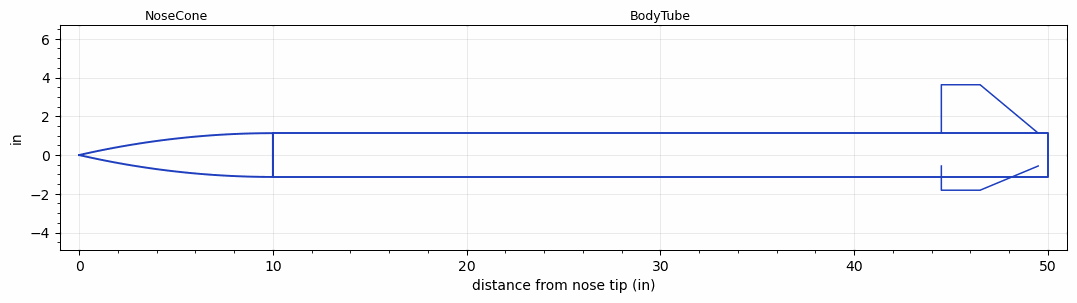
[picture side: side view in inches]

<RASAeroDocument>
 <FileVersion>2</FileVersion>
 <RocketDesign>
  <NoseCone>
   <Length>10</Length>
   <Diameter>2.26</Diameter>
   <Shape>Tangent Ogive</Shape>
   <Location>0</Location>
  </NoseCone>
  <BodyTube>
   <Length>39.9999</Length>
   <Diameter>2.26</Diameter>
   <Location>10</Location>
   <Fin>
    <Count>3</Count>
    <Chord>5</Chord>
    <Span>2.5</Span>
    <SweepDistance>0</SweepDistance>
    <TipChord>2</TipChord>
    <Thickness>0.125</Thickness>
    <Location>5.5</Location>
    <AirfoilSection>Square</AirfoilSection>
   </Fin>
  </BodyTube>
  <Surface>Smooth (Zero Roughness)</Surface>
  <ModifiedBarrowman>False</ModifiedBarrowman>
  <Turbulence>True</Turbulence>
  <UseBooster1>False</UseBooster1>
  <UseBooster2>False</UseBooster2>
  <Comments>Controlled aerodynamic investigation: Ssq-unswept</Comments>
 </RocketDesign>
 <LaunchSite>
  <Altitude>0</Altitude>
  <Pressure>29.9214</Pressure>
  <RodAngle>0</RodAngle>
  <RodLength>6.5617</RodLength>
  <Temperature>59</Temperature>
  <WindSpeed>0</WindSpeed>
 </LaunchSite>
 <Recovery>
  <Altitude1>656.168</Altitude1>
  <Altitude2>0</Altitude2>
  <DeviceType1>Parachute</DeviceType1>
  <DeviceType2>None</DeviceType2>
  <Event1>True</Event1>
  <Event2>False</Event2>
  <Size1>24</Size1>
  <Size2>0</Size2>
  <EventType1>Apogee</EventType1>
  <EventType2>None</EventType2>
  <CD1>0.8</CD1>
  <CD2>0</CD2>
 </Recovery>
 <SimulationList>
  <Simulation>
   <SustainerEngine>I500T-14A  (AT)</SustainerEngine>
   <SustainerLaunchWt>3.4833</SustainerLaunchWt>
   <SustainerCG>32.8777</SustainerCG>
   <SustainerIgnitionDelay>0</SustainerIgnitionDelay>
   <Booster1SeparationDelay>0</Booster1SeparationDelay>
   <Booster1IgnitionDelay>0</Booster1IgnitionDelay>
   <IncludeBooster1>False</IncludeBooster1>
   <Booster2Delay>0</Booster2Delay>
   <IncludeBooster2>False</IncludeBooster2>
   <TimetoApogee>14.08023</TimetoApogee>
   <MaxAltitude>5003.284</MaxAltitude>
   <MaxVelocity>1147.371</MaxVelocity>
  </Simulation>
  <Simulation>
   <SustainerEngine>J570W  (AT)</SustainerEngine>
   <SustainerLaunchWt>4.1582</SustainerLaunchWt>
   <SustainerCG>33.3758</SustainerCG>
   <SustainerIgnitionDelay>0</SustainerIgnitionDelay>
   <Booster1SeparationDelay>0</Booster1SeparationDelay>
   <Booster1IgnitionDelay>0</Booster1IgnitionDelay>
   <IncludeBooster1>False</IncludeBooster1>
   <Booster2Delay>0</Booster2Delay>
   <IncludeBooster2>False</IncludeBooster2>
   <TimetoApogee>15.26025</TimetoApogee>
   <MaxAltitude>6657.001</MaxAltitude>
   <MaxVelocity>1434.941</MaxVelocity>
  </Simulation>
 </SimulationList>
</RASAeroDocument>
